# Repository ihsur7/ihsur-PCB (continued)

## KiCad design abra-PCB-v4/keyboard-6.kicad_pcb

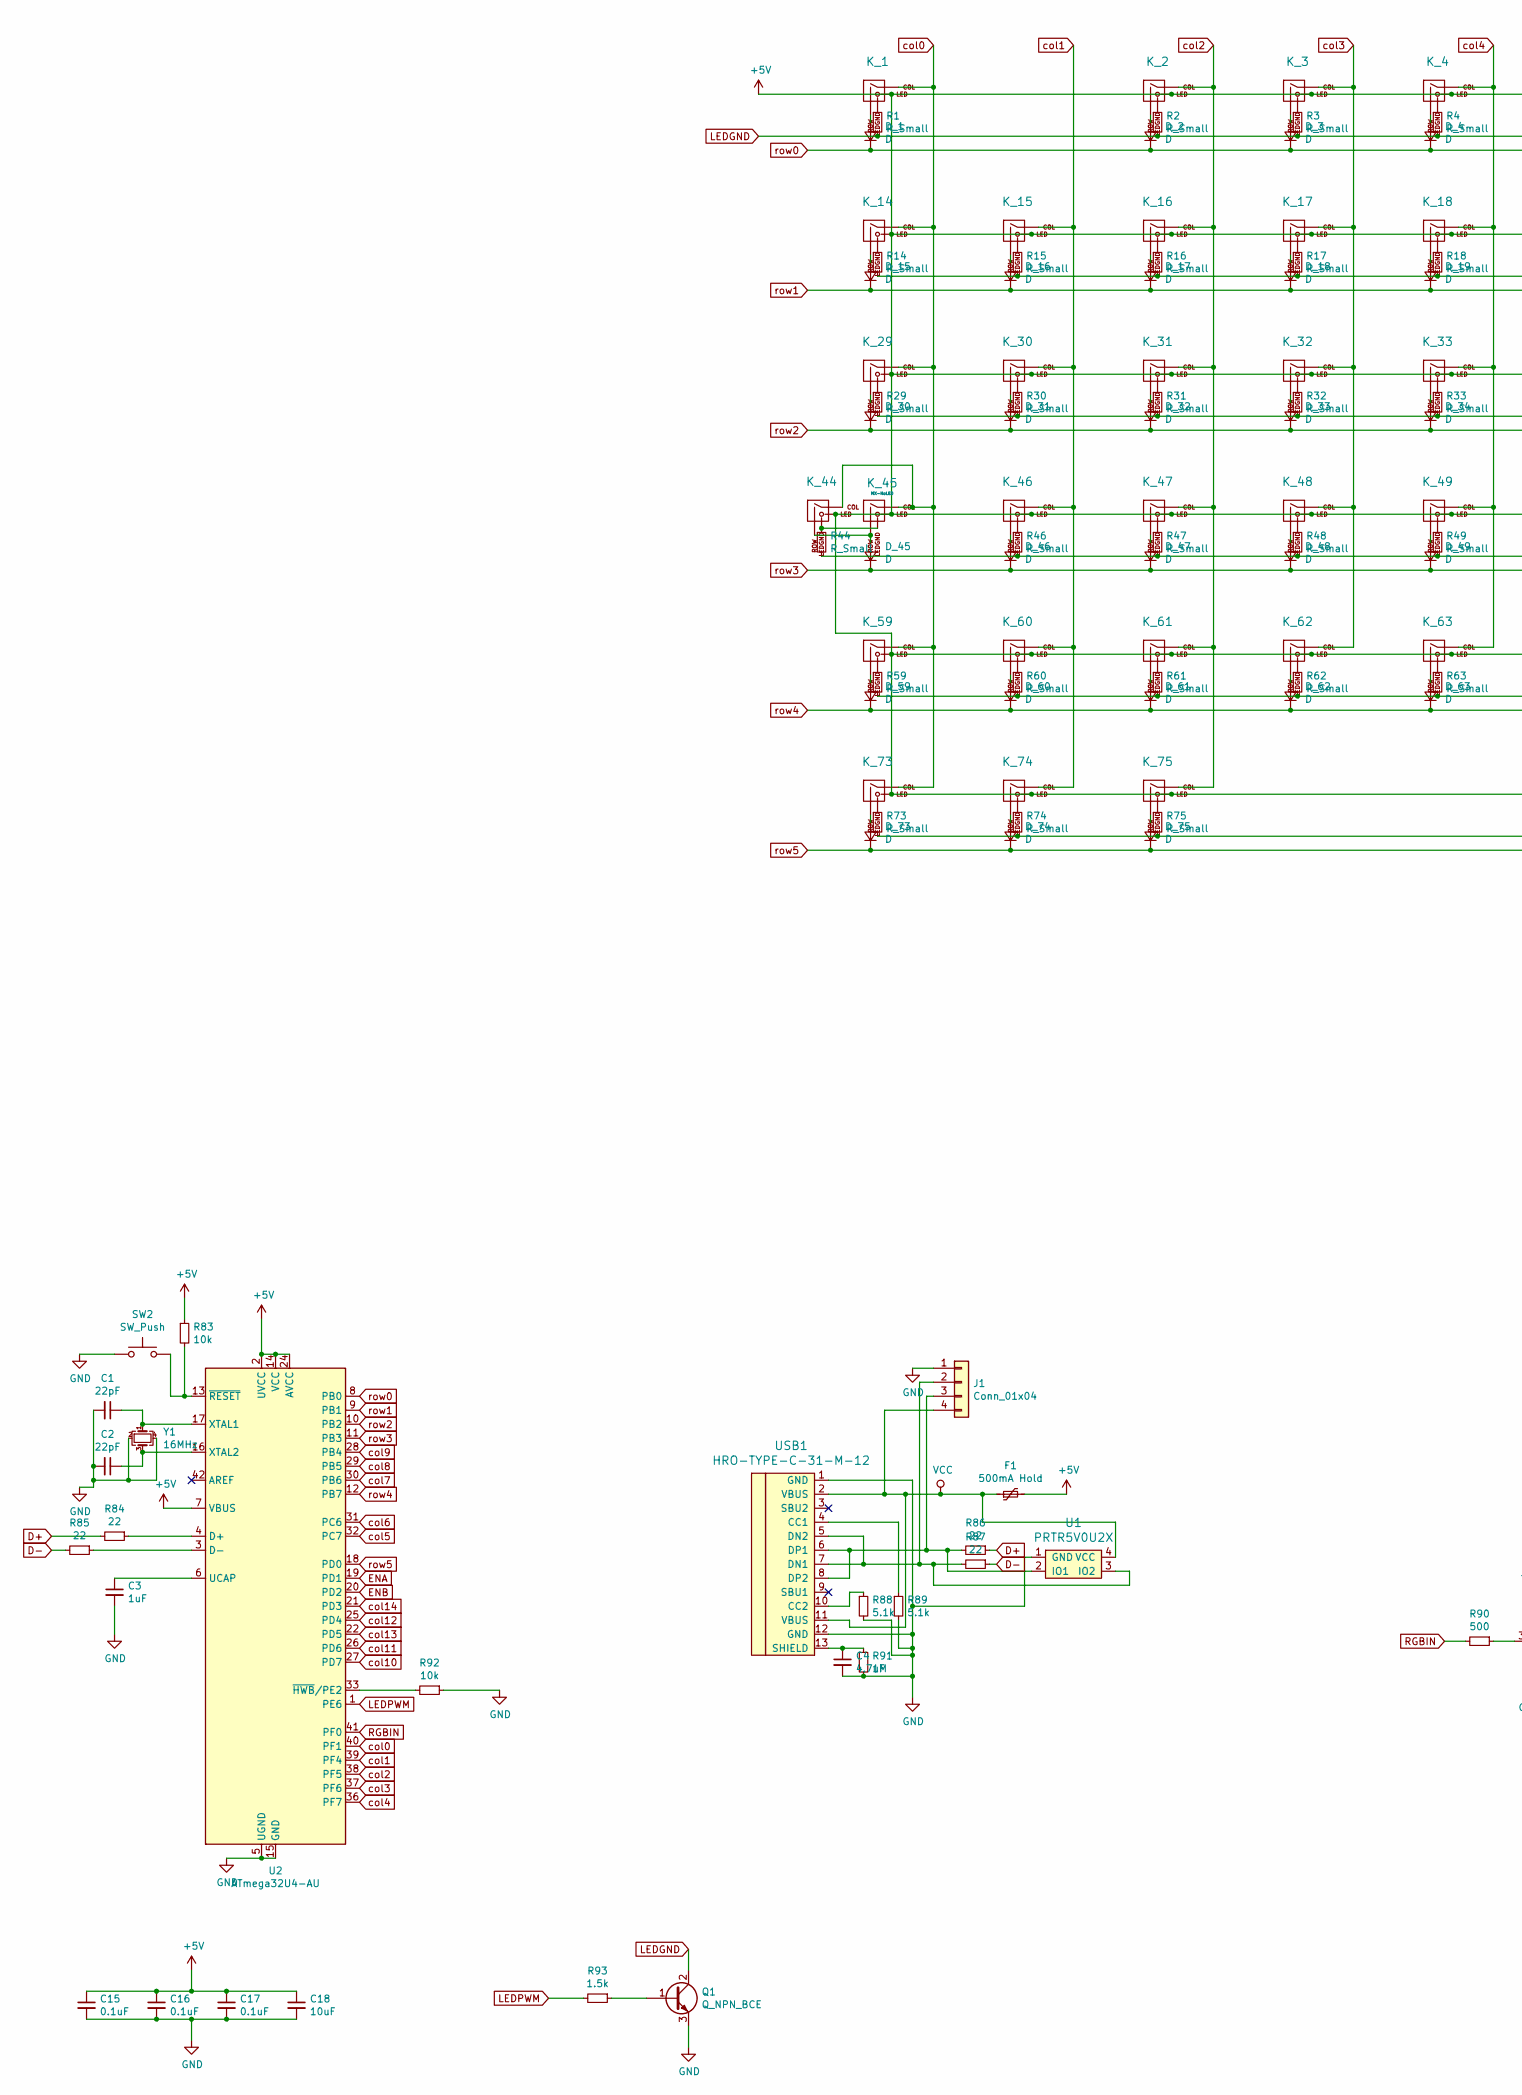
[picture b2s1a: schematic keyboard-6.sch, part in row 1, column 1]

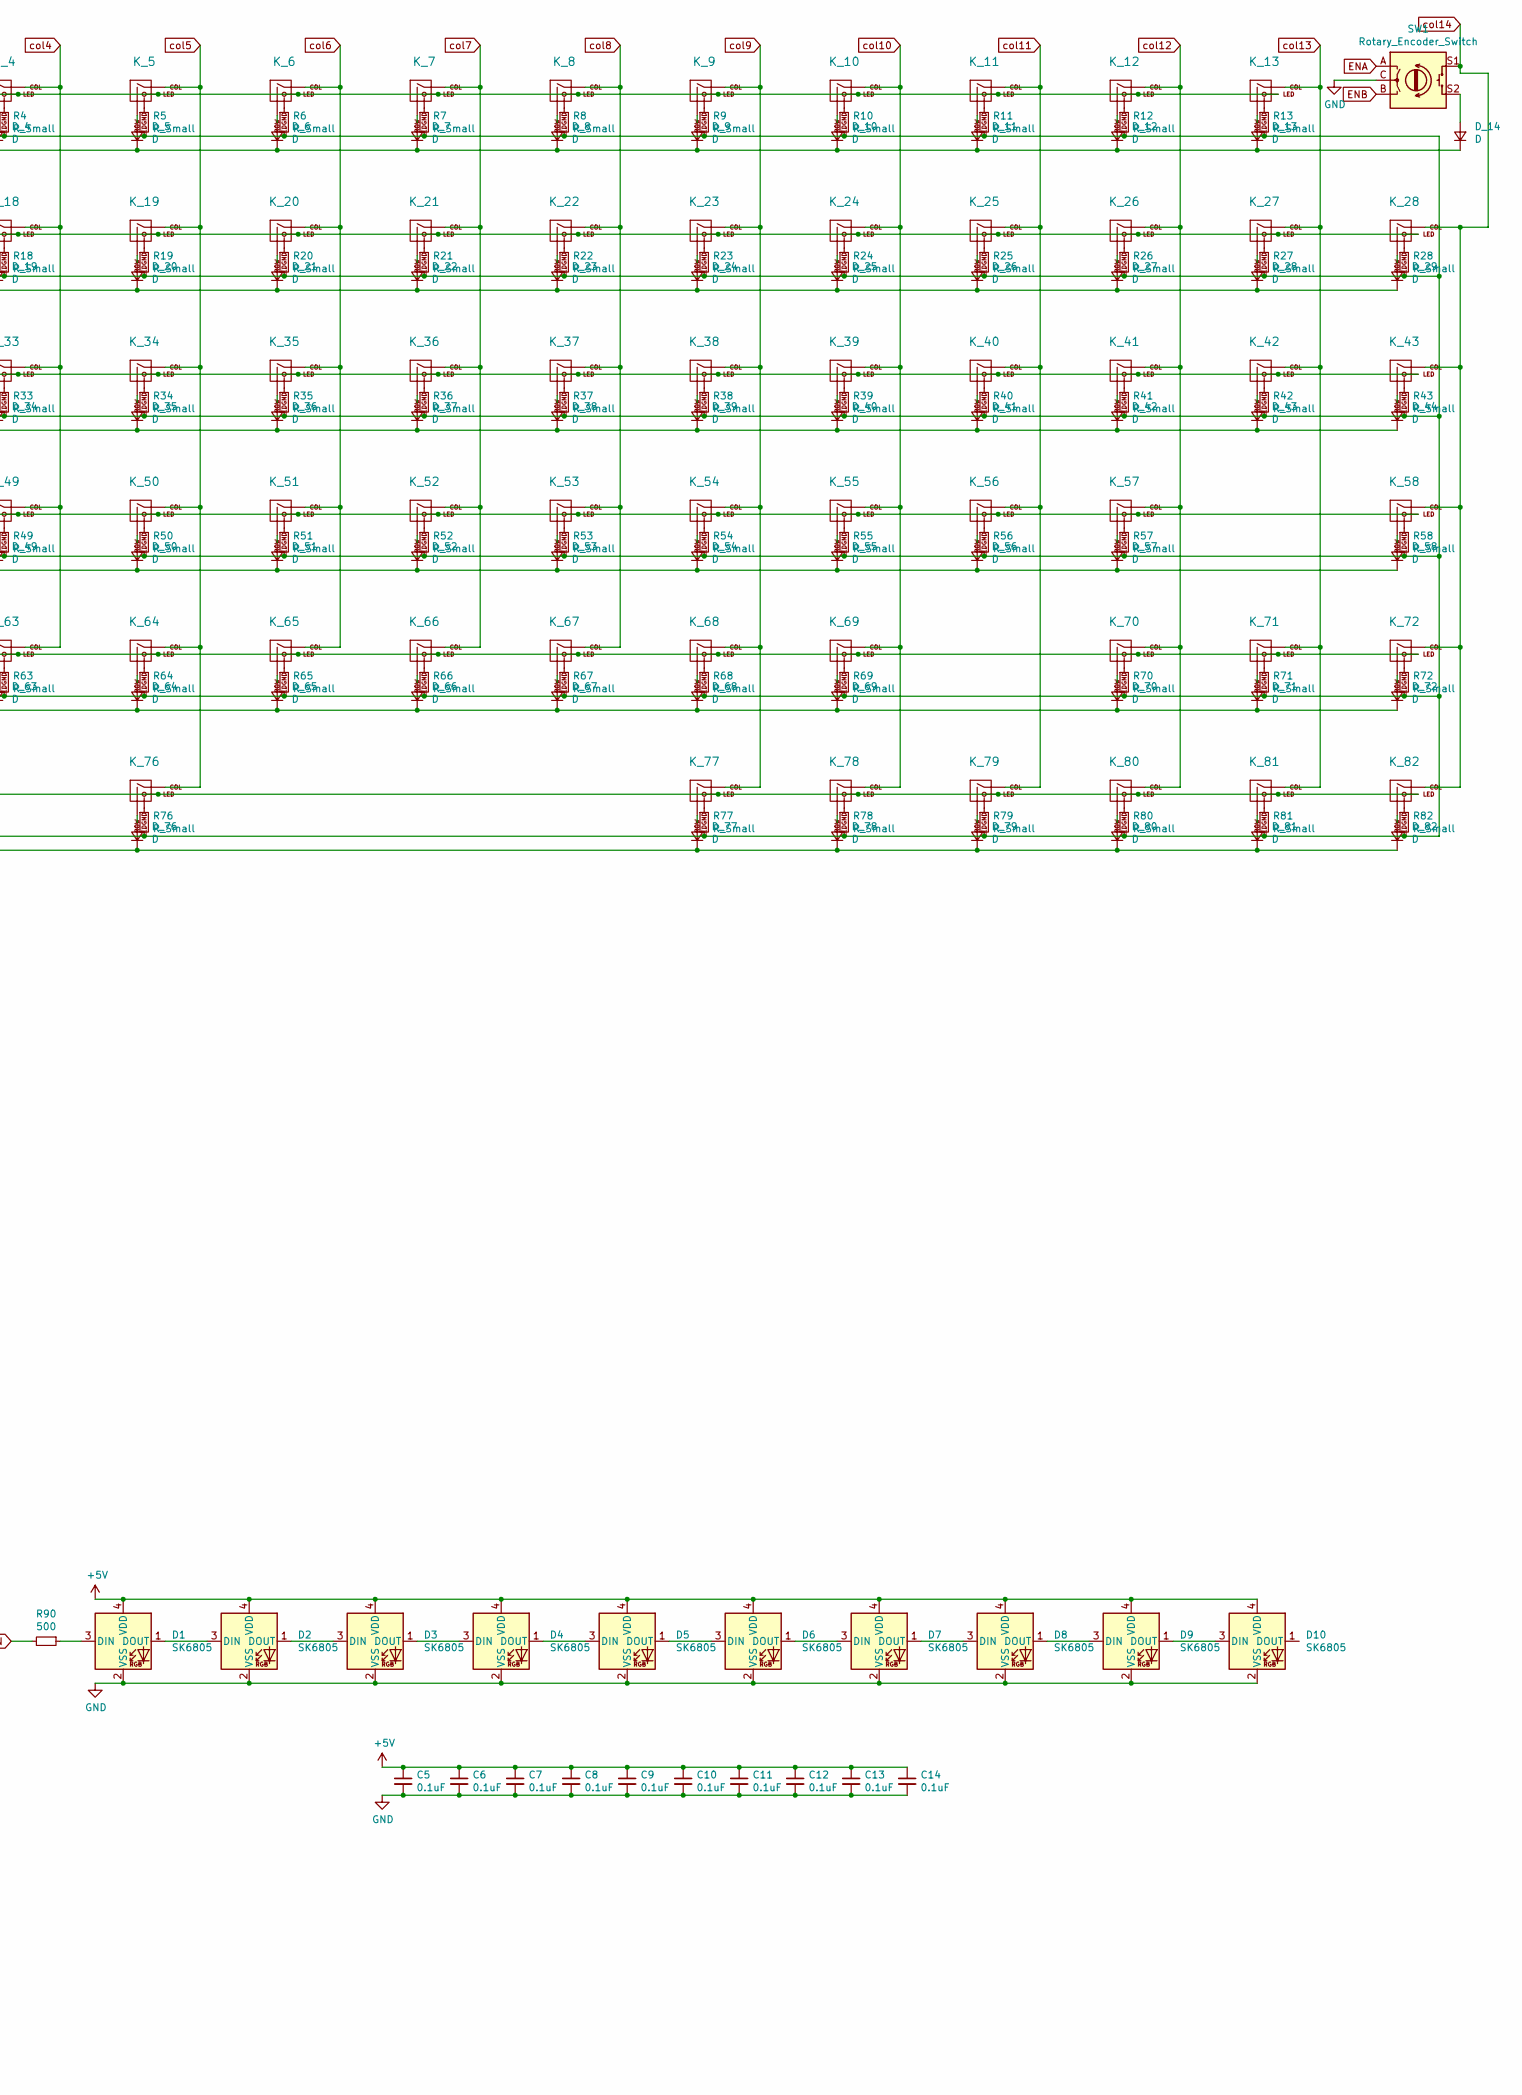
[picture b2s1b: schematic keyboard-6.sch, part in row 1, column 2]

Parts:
C1, C2: 22pF; C_0805_2012Metric
C3: 1uF; C_0805_2012Metric
C4: 4.7uF; C_0805_2012Metric
C5, C6, C7, C8, C9, C10, C11, C12, C13, C14, C15, C16, C17: 0.1uF; C_0805_2012Metric
C18: 10uF; C_0805_2012Metric
D1, D2, D3, D4, D5, D6, D7, D8, D9, D10: SK6805; LED_SK6812_EC15_1.5x1.5mm
D_1, D_2, D_3, D_4, D_5, D_6, D_7, D_8, D_9, D_10, D_11, D_12, D_13, D_14, D_15, D_16, D_17, D_18, D_19, D_20, D_21, D_22, D_23, D_24, D_25, D_26, D_27, D_28, D_29, D_30, D_31, D_32, D_33, D_34, D_35, D_36, D_37, D_38, D_39, D_40, D_41, D_42, D_43, D_44, D_45, D_46, D_47, D_48, D_49, D_50, D_51, D_52, D_53, D_54, D_55, D_56, D_57, D_58, D_59, D_60, D_61, D_62, D_63, D_64, D_65, D_66, D_67, D_68, D_69, D_70, D_71, D_72, D_73, D_74, D_75, D_76, D_77, D_78, D_79, D_80, D_81, D_82: D; D_SOD-123
F1: 500mA Hold; Fuse_1812_4532
J1: Conn_01x04; PinHeader_1x04_P2.54mm_Vertical_SMD_Pin1Left
K_1, K_2, K_3, K_4, K_5, K_6, K_7, K_8, K_9, K_10, K_11, K_12, K_13, K_14, K_15, K_16, K_17, K_18, K_19, K_20, K_21, K_22, K_23, K_24, K_25, K_26, K_28, K_30, K_31, K_32, K_33, K_34, K_35, K_36, K_37, K_38, K_39, K_40, K_41, K_43, K_46, K_47, K_48, K_49, K_50, K_51, K_52, K_53, K_54, K_55, K_56, K_58, K_60, K_61, K_62, K_63, K_64, K_65, K_66, K_67, K_68, K_69, K_71, K_72, K_77, K_78, K_79, K_80, K_81, K_82: KEYSW; MXOnly-1U
K_27: KEYSW; MXOnly-2U
K_29, K_42: KEYSW; MXOnly-1.5U
K_44, K_70: KEYSW; MXOnly-1.75U
K_45: MX-NoLED; MXOnly-1.75U
K_57, K_59: KEYSW; MXOnly-2.25U
K_73, K_74, K_75: KEYSW; MXOnly-1.25U
K_76: KEYSW; MXOnly-6.25U
Q1: Q_NPN_BCE; SOT-223-3_TabPin2
R1, R2, R3, R4, R5, R6, R7, R8, R9, R10, R11, R12, R13, R14, R15, R16, R17, R18, R19, R20, R21, R22, R23, R24, R25, R26, R27, R28, R29, R30, R31, R32, R33, R34, R35, R36, R37, R38, R39, R40, R41, R42, R43, R44, R46, R47, R48, R49, R50, R51, R52, R53, R54, R55, R56, R57, R58, R59, R60, R61, R62, R63, R64, R65, R66, R67, R68, R69, R70, R71, R72, R73, R74, R75, R76, R77, R78, R79, R80, R81, R82: R_Small; R_SMD_1206
R83, R92: 10k; R_SMD_1206
R84, R85, R86, R87: 22; R_SMD_1206
R88, R89: 5.1k; R_SMD_1206
R90: 500; R_SMD_1206
R91: 1M; R_SMD_1206
R93: 1.5k; R_SMD_1206
SW1: Rotary_Encoder_Switch; RotaryEncoder_Alps_EC11E-Switch_Vertical_H20mm
SW2: SW_Push; SW_SPST_3x3
U1: PRTR5V0U2X; SOT143B
U2: ATmega32U4-AU; TQFP-44_10x10mm_P0.8mm
USB1: HRO-TYPE-C-31-M-12; HRO-TYPE-C-31-M-12-HandSoldering
Y1: 16MHz; Crystal_SMD_3225-4pin_3.2x2.5mm

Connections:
+5V: C5.1, C6.1, C7.1, C8.1, C9.1, C10.1, C11.1, C12.1, C13.1, C14.1, C15.1, C16.1, C17.1, C18.1, D1.4 (VDD), D2.4 (VDD), D3.4 (VDD), D4.4 (VDD), D5.4 (VDD), D6.4 (VDD), D7.4 (VDD), D8.4 (VDD), D9.4 (VDD), D10.4 (VDD), F1.2, K_1.3 (LED), K_2.3 (LED), K_3.3 (LED), K_4.3 (LED), K_5.3 (LED), K_6.3 (LED), K_7.3 (LED), K_8.3 (LED), K_9.3 (LED), K_10.3 (LED), K_11.3 (LED), K_12.3 (LED), K_13.3 (LED), K_14.3 (LED), K_15.3 (LED), K_16.3 (LED), K_17.3 (LED), K_18.3 (LED), K_19.3 (LED), K_20.3 (LED), K_21.3 (LED), K_22.3 (LED), K_23.3 (LED), K_24.3 (LED), K_25.3 (LED), K_26.3 (LED), K_27.3 (LED), K_28.3 (LED), K_29.3 (LED), K_30.3 (LED), K_31.3 (LED), K_32.3 (LED), K_33.3 (LED), K_34.3 (LED), K_35.3 (LED), K_36.3 (LED), K_37.3 (LED), K_38.3 (LED), K_39.3 (LED), K_40.3 (LED), K_41.3 (LED), K_42.3 (LED), K_43.3 (LED), K_44.3 (LED), K_45.3 (LED), K_46.3 (LED), K_47.3 (LED), K_48.3 (LED), K_49.3 (LED), K_50.3 (LED), K_51.3 (LED), K_52.3 (LED), K_53.3 (LED), K_54.3 (LED), K_55.3 (LED), K_56.3 (LED), K_57.3 (LED), K_58.3 (LED), K_59.3 (LED), K_60.3 (LED), K_61.3 (LED), K_62.3 (LED), K_63.3 (LED), K_64.3 (LED), K_65.3 (LED), K_66.3 (LED), K_67.3 (LED), K_68.3 (LED), K_69.3 (LED), K_70.3 (LED), K_71.3 (LED), K_72.3 (LED), K_73.3 (LED), K_74.3 (LED), K_75.3 (LED), K_76.3 (LED), K_77.3 (LED), K_78.3 (LED), K_79.3 (LED), K_80.3 (LED), K_81.3 (LED), K_82.3 (LED), R83.1, U2.2 (UVCC), U2.7 (VBUS), U2.14 (VCC), U2.24 (AVCC), U2.34 (VCC), U2.44 (AVCC)
D+: R84.2, R86.1
D-: R85.2, R87.1
ENA: SW1.A, U2.19 (PD1)
ENB: SW1.B, U2.20 (PD2)
GND: C1.2, C2.2, C3.2, C4.2, C5.2, C6.2, C7.2, C8.2, C9.2, C10.2, C11.2, C12.2, C13.2, C14.2, C15.2, C16.2, C17.2, C18.2, D1.2 (VSS), D2.2 (VSS), D3.2 (VSS), D4.2 (VSS), D5.2 (VSS), D6.2 (VSS), D7.2 (VSS), D8.2 (VSS), D9.2 (VSS), D10.2 (VSS), J1.1, Q1.3 (E), R88.2, R89.2, R91.2, R92.1, SW1.C, SW2.1, U1.1 (GND), U2.5 (UGND), U2.15 (GND), U2.23 (GND), U2.35 (GND), U2.43 (GND), USB1.1 (GND), USB1.12 (GND), Y1.2, Y1.4
LEDGND: Q1.2 (C), R1.2, R2.2, R3.2, R4.2, R5.2, R6.2, R7.2, R8.2, R9.2, R10.2, R11.2, R12.2, R13.2, R14.2, R15.2, R16.2, R17.2, R18.2, R19.2, R20.2, R21.2, R22.2, R23.2, R24.2, R25.2, R26.2, R27.2, R28.2, R29.2, R30.2, R31.2, R32.2, R33.2, R34.2, R35.2, R36.2, R37.2, R38.2, R39.2, R40.2, R41.2, R42.2, R43.2, R44.2, R46.2, R47.2, R48.2, R49.2, R50.2, R51.2, R52.2, R53.2, R54.2, R55.2, R56.2, R57.2, R58.2, R59.2, R60.2, R61.2, R62.2, R63.2, R64.2, R65.2, R66.2, R67.2, R68.2, R69.2, R70.2, R71.2, R72.2, R73.2, R74.2, R75.2, R76.2, R77.2, R78.2, R79.2, R80.2, R81.2, R82.2
LEDPWM: R93.2, U2.1 (PE6)
unnamed: C1.1, U2.17 (XTAL1), Y1.1
unnamed: C2.1, U2.16 (XTAL2), Y1.3
unnamed: C3.1, U2.6 (UCAP)
unnamed: C4.1, R91.1, USB1.13 (SHIELD)
unnamed: D1.1 (DOUT), D2.3 (DIN)
unnamed: D1.3 (DIN), R90.1
unnamed: D2.1 (DOUT), D3.3 (DIN)
unnamed: D3.1 (DOUT), D4.3 (DIN)
unnamed: D4.1 (DOUT), D5.3 (DIN)
unnamed: D5.1 (DOUT), D6.3 (DIN)
unnamed: D6.1 (DOUT), D7.3 (DIN)
unnamed: D7.1 (DOUT), D8.3 (DIN)
unnamed: D8.1 (DOUT), D9.3 (DIN)
unnamed: D9.1 (DOUT), D10.3 (DIN)
unnamed: D_1.2 (A), K_1.2 (ROW)
unnamed: D_2.2 (A), K_2.2 (ROW)
unnamed: D_3.2 (A), K_3.2 (ROW)
unnamed: D_4.2 (A), K_4.2 (ROW)
unnamed: D_5.2 (A), K_5.2 (ROW)
unnamed: D_6.2 (A), K_6.2 (ROW)
unnamed: D_7.2 (A), K_7.2 (ROW)
unnamed: D_8.2 (A), K_8.2 (ROW)
unnamed: D_9.2 (A), K_9.2 (ROW)
unnamed: D_10.2 (A), K_10.2 (ROW)
unnamed: D_11.2 (A), K_11.2 (ROW)
unnamed: D_12.2 (A), K_12.2 (ROW)
unnamed: D_13.2 (A), K_13.2 (ROW)
unnamed: D_14.2 (A), SW1.S2
unnamed: D_15.2 (A), K_14.2 (ROW)
unnamed: D_16.2 (A), K_15.2 (ROW)
unnamed: D_17.2 (A), K_16.2 (ROW)
unnamed: D_18.2 (A), K_17.2 (ROW)
unnamed: D_19.2 (A), K_18.2 (ROW)
unnamed: D_20.2 (A), K_19.2 (ROW)
unnamed: D_21.2 (A), K_20.2 (ROW)
unnamed: D_22.2 (A), K_21.2 (ROW)
unnamed: D_23.2 (A), K_22.2 (ROW)
unnamed: D_24.2 (A), K_23.2 (ROW)
unnamed: D_25.2 (A), K_24.2 (ROW)
unnamed: D_26.2 (A), K_25.2 (ROW)
unnamed: D_27.2 (A), K_26.2 (ROW)
unnamed: D_28.2 (A), K_27.2 (ROW)
unnamed: D_29.2 (A), K_28.2 (ROW)
unnamed: D_30.2 (A), K_29.2 (ROW)
unnamed: D_31.2 (A), K_30.2 (ROW)
unnamed: D_32.2 (A), K_31.2 (ROW)
unnamed: D_33.2 (A), K_32.2 (ROW)
unnamed: D_34.2 (A), K_33.2 (ROW)
unnamed: D_35.2 (A), K_34.2 (ROW)
unnamed: D_36.2 (A), K_35.2 (ROW)
unnamed: D_37.2 (A), K_36.2 (ROW)
unnamed: D_38.2 (A), K_37.2 (ROW)
unnamed: D_39.2 (A), K_38.2 (ROW)
unnamed: D_40.2 (A), K_39.2 (ROW)
unnamed: D_41.2 (A), K_40.2 (ROW)
unnamed: D_42.2 (A), K_41.2 (ROW)
unnamed: D_43.2 (A), K_42.2 (ROW)
unnamed: D_44.2 (A), K_43.2 (ROW)
unnamed: D_45.2 (A), K_44.2 (ROW), K_45.2 (ROW)
unnamed: D_46.2 (A), K_46.2 (ROW)
unnamed: D_47.2 (A), K_47.2 (ROW)
unnamed: D_48.2 (A), K_48.2 (ROW)
unnamed: D_49.2 (A), K_49.2 (ROW)
unnamed: D_50.2 (A), K_50.2 (ROW)
unnamed: D_51.2 (A), K_51.2 (ROW)
unnamed: D_52.2 (A), K_52.2 (ROW)
unnamed: D_53.2 (A), K_53.2 (ROW)
unnamed: D_54.2 (A), K_54.2 (ROW)
unnamed: D_55.2 (A), K_55.2 (ROW)
unnamed: D_56.2 (A), K_56.2 (ROW)
unnamed: D_57.2 (A), K_57.2 (ROW)
unnamed: D_58.2 (A), K_58.2 (ROW)
unnamed: D_59.2 (A), K_59.2 (ROW)
unnamed: D_60.2 (A), K_60.2 (ROW)
unnamed: D_61.2 (A), K_61.2 (ROW)
unnamed: D_62.2 (A), K_62.2 (ROW)
unnamed: D_63.2 (A), K_63.2 (ROW)
unnamed: D_64.2 (A), K_64.2 (ROW)
unnamed: D_65.2 (A), K_65.2 (ROW)
unnamed: D_66.2 (A), K_66.2 (ROW)
unnamed: D_67.2 (A), K_67.2 (ROW)
unnamed: D_68.2 (A), K_68.2 (ROW)
unnamed: D_69.2 (A), K_69.2 (ROW)
unnamed: D_70.2 (A), K_70.2 (ROW)
unnamed: D_71.2 (A), K_71.2 (ROW)
unnamed: D_72.2 (A), K_72.2 (ROW)
unnamed: D_73.2 (A), K_73.2 (ROW)
unnamed: D_74.2 (A), K_74.2 (ROW)
unnamed: D_75.2 (A), K_75.2 (ROW)
unnamed: D_76.2 (A), K_76.2 (ROW)
unnamed: D_77.2 (A), K_77.2 (ROW)
unnamed: D_78.2 (A), K_78.2 (ROW)
unnamed: D_79.2 (A), K_79.2 (ROW)
unnamed: D_80.2 (A), K_80.2 (ROW)
unnamed: D_81.2 (A), K_81.2 (ROW)
unnamed: D_82.2 (A), K_82.2 (ROW)
unnamed: J1.2, R87.2, U1.3 (IO2), USB1.5 (DN2), USB1.7 (DN1)
unnamed: J1.3, R86.2, U1.2 (IO1), USB1.6 (DP1), USB1.8 (DP2)
unnamed: K_1.4 (LEDGND), R1.1
unnamed: K_2.4 (LEDGND), R2.1
unnamed: K_3.4 (LEDGND), R3.1
unnamed: K_4.4 (LEDGND), R4.1
unnamed: K_5.4 (LEDGND), R5.1
unnamed: K_6.4 (LEDGND), R6.1
unnamed: K_7.4 (LEDGND), R7.1
unnamed: K_8.4 (LEDGND), R8.1
unnamed: K_9.4 (LEDGND), R9.1
unnamed: K_10.4 (LEDGND), R10.1
unnamed: K_11.4 (LEDGND), R11.1
unnamed: K_12.4 (LEDGND), R12.1
unnamed: K_13.4 (LEDGND), R13.1
unnamed: K_14.4 (LEDGND), R14.1
unnamed: K_15.4 (LEDGND), R15.1
unnamed: K_16.4 (LEDGND), R16.1
unnamed: K_17.4 (LEDGND), R17.1
unnamed: K_18.4 (LEDGND), R18.1
unnamed: K_19.4 (LEDGND), R19.1
unnamed: K_20.4 (LEDGND), R20.1
unnamed: K_21.4 (LEDGND), R21.1
unnamed: K_22.4 (LEDGND), R22.1
unnamed: K_23.4 (LEDGND), R23.1
unnamed: K_24.4 (LEDGND), R24.1
unnamed: K_25.4 (LEDGND), R25.1
unnamed: K_26.4 (LEDGND), R26.1
unnamed: K_27.4 (LEDGND), R27.1
unnamed: K_28.4 (LEDGND), R28.1
unnamed: K_29.4 (LEDGND), R29.1
unnamed: K_30.4 (LEDGND), R30.1
unnamed: K_31.4 (LEDGND), R31.1
unnamed: K_32.4 (LEDGND), R32.1
unnamed: K_33.4 (LEDGND), R33.1
unnamed: K_34.4 (LEDGND), R34.1
unnamed: K_35.4 (LEDGND), R35.1
unnamed: K_36.4 (LEDGND), R36.1
unnamed: K_37.4 (LEDGND), R37.1
unnamed: K_38.4 (LEDGND), R38.1
unnamed: K_39.4 (LEDGND), R39.1
unnamed: K_40.4 (LEDGND), R40.1
unnamed: K_41.4 (LEDGND), R41.1
unnamed: K_42.4 (LEDGND), R42.1
unnamed: K_43.4 (LEDGND), R43.1
unnamed: K_44.4 (LEDGND), K_45.4 (LEDGND), R44.1
unnamed: K_46.4 (LEDGND), R46.1
unnamed: K_47.4 (LEDGND), R47.1
unnamed: K_48.4 (LEDGND), R48.1
unnamed: K_49.4 (LEDGND), R49.1
unnamed: K_50.4 (LEDGND), R50.1
unnamed: K_51.4 (LEDGND), R51.1
unnamed: K_52.4 (LEDGND), R52.1
unnamed: K_53.4 (LEDGND), R53.1
unnamed: K_54.4 (LEDGND), R54.1
unnamed: K_55.4 (LEDGND), R55.1
unnamed: K_56.4 (LEDGND), R56.1
unnamed: K_57.4 (LEDGND), R57.1
unnamed: K_58.4 (LEDGND), R58.1
unnamed: K_59.4 (LEDGND), R59.1
unnamed: K_60.4 (LEDGND), R60.1
unnamed: K_61.4 (LEDGND), R61.1
unnamed: K_62.4 (LEDGND), R62.1
unnamed: K_63.4 (LEDGND), R63.1
unnamed: K_64.4 (LEDGND), R64.1
unnamed: K_65.4 (LEDGND), R65.1
unnamed: K_66.4 (LEDGND), R66.1
unnamed: K_67.4 (LEDGND), R67.1
unnamed: K_68.4 (LEDGND), R68.1
unnamed: K_69.4 (LEDGND), R69.1
unnamed: K_70.4 (LEDGND), R70.1
unnamed: K_71.4 (LEDGND), R71.1
unnamed: K_72.4 (LEDGND), R72.1
unnamed: K_73.4 (LEDGND), R73.1
unnamed: K_74.4 (LEDGND), R74.1
unnamed: K_75.4 (LEDGND), R75.1
unnamed: K_76.4 (LEDGND), R76.1
unnamed: K_77.4 (LEDGND), R77.1
unnamed: K_78.4 (LEDGND), R78.1
unnamed: K_79.4 (LEDGND), R79.1
unnamed: K_80.4 (LEDGND), R80.1
unnamed: K_81.4 (LEDGND), R81.1
unnamed: K_82.4 (LEDGND), R82.1
unnamed: Q1.1 (B), R93.1
unnamed: R83.2, SW2.2, U2.13 (~RESET)
unnamed: R84.1, U2.4 (D+)
unnamed: R85.1, U2.3 (D-)
unnamed: R88.1, USB1.10 (CC2)
unnamed: R89.1, USB1.4 (CC1)
unnamed: R92.2, U2.33 (~HWB~/PE2)
RGBIN: R90.2, U2.41 (PF0)
VCC: F1.1, J1.4, U1.4 (VCC), USB1.2 (VBUS), USB1.11 (VBUS)
col0: K_1.1 (COL), K_14.1 (COL), K_29.1 (COL), K_44.1 (COL), K_45.1 (COL), K_59.1 (COL), K_73.1 (COL), U2.40 (PF1)
col1: K_15.1 (COL), K_30.1 (COL), K_46.1 (COL), K_60.1 (COL), K_74.1 (COL), U2.39 (PF4)
col2: K_2.1 (COL), K_16.1 (COL), K_31.1 (COL), K_47.1 (COL), K_61.1 (COL), K_75.1 (COL), U2.38 (PF5)
col3: K_3.1 (COL), K_17.1 (COL), K_32.1 (COL), K_48.1 (COL), K_62.1 (COL), U2.37 (PF6)
col4: K_4.1 (COL), K_18.1 (COL), K_33.1 (COL), K_49.1 (COL), K_63.1 (COL), U2.36 (PF7)
col5: K_5.1 (COL), K_19.1 (COL), K_34.1 (COL), K_50.1 (COL), K_64.1 (COL), K_76.1 (COL), U2.32 (PC7)
col6: K_6.1 (COL), K_20.1 (COL), K_35.1 (COL), K_51.1 (COL), K_65.1 (COL), U2.31 (PC6)
col7: K_7.1 (COL), K_21.1 (COL), K_36.1 (COL), K_52.1 (COL), K_66.1 (COL), U2.30 (PB6)
col8: K_8.1 (COL), K_22.1 (COL), K_37.1 (COL), K_53.1 (COL), K_67.1 (COL), U2.29 (PB5)
col9: K_9.1 (COL), K_23.1 (COL), K_38.1 (COL), K_54.1 (COL), K_68.1 (COL), K_77.1 (COL), U2.28 (PB4)
col10: K_10.1 (COL), K_24.1 (COL), K_39.1 (COL), K_55.1 (COL), K_69.1 (COL), K_78.1 (COL), U2.27 (PD7)
col11: K_11.1 (COL), K_25.1 (COL), K_40.1 (COL), K_56.1 (COL), K_79.1 (COL), U2.26 (PD6)
col12: K_12.1 (COL), K_26.1 (COL), K_41.1 (COL), K_57.1 (COL), K_70.1 (COL), K_80.1 (COL), U2.25 (PD4)
col13: K_13.1 (COL), K_27.1 (COL), K_42.1 (COL), K_71.1 (COL), K_81.1 (COL), U2.22 (PD5)
col14: K_28.1 (COL), K_43.1 (COL), K_58.1 (COL), K_72.1 (COL), K_82.1 (COL), SW1.S1, U2.21 (PD3)
row0: D_1.1 (K), D_2.1 (K), D_3.1 (K), D_4.1 (K), D_5.1 (K), D_6.1 (K), D_7.1 (K), D_8.1 (K), D_9.1 (K), D_10.1 (K), D_11.1 (K), D_12.1 (K), D_13.1 (K), D_14.1 (K), U2.8 (PB0)
row1: D_15.1 (K), D_16.1 (K), D_17.1 (K), D_18.1 (K), D_19.1 (K), D_20.1 (K), D_21.1 (K), D_22.1 (K), D_23.1 (K), D_24.1 (K), D_25.1 (K), D_26.1 (K), D_27.1 (K), D_28.1 (K), D_29.1 (K), U2.9 (PB1)
row2: D_30.1 (K), D_31.1 (K), D_32.1 (K), D_33.1 (K), D_34.1 (K), D_35.1 (K), D_36.1 (K), D_37.1 (K), D_38.1 (K), D_39.1 (K), D_40.1 (K), D_41.1 (K), D_42.1 (K), D_43.1 (K), D_44.1 (K), U2.10 (PB2)
row3: D_45.1 (K), D_46.1 (K), D_47.1 (K), D_48.1 (K), D_49.1 (K), D_50.1 (K), D_51.1 (K), D_52.1 (K), D_53.1 (K), D_54.1 (K), D_55.1 (K), D_56.1 (K), D_57.1 (K), D_58.1 (K), U2.11 (PB3)
row4: D_59.1 (K), D_60.1 (K), D_61.1 (K), D_62.1 (K), D_63.1 (K), D_64.1 (K), D_65.1 (K), D_66.1 (K), D_67.1 (K), D_68.1 (K), D_69.1 (K), D_70.1 (K), D_71.1 (K), D_72.1 (K), U2.12 (PB7)
row5: D_73.1 (K), D_74.1 (K), D_75.1 (K), D_76.1 (K), D_77.1 (K), D_78.1 (K), D_79.1 (K), D_80.1 (K), D_81.1 (K), D_82.1 (K), U2.18 (PD0)

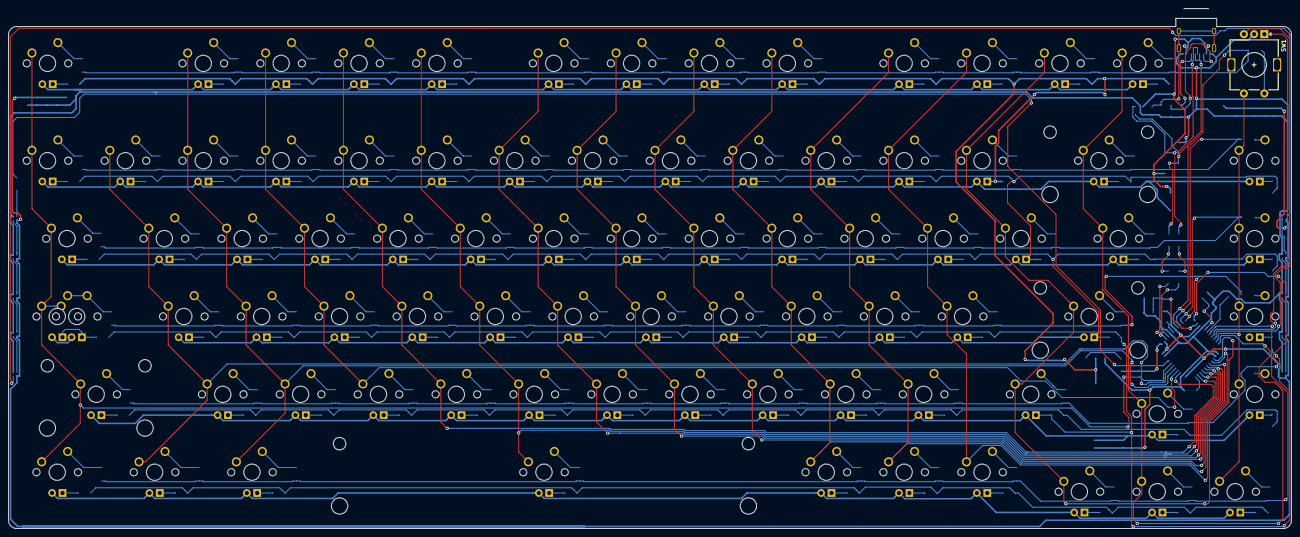
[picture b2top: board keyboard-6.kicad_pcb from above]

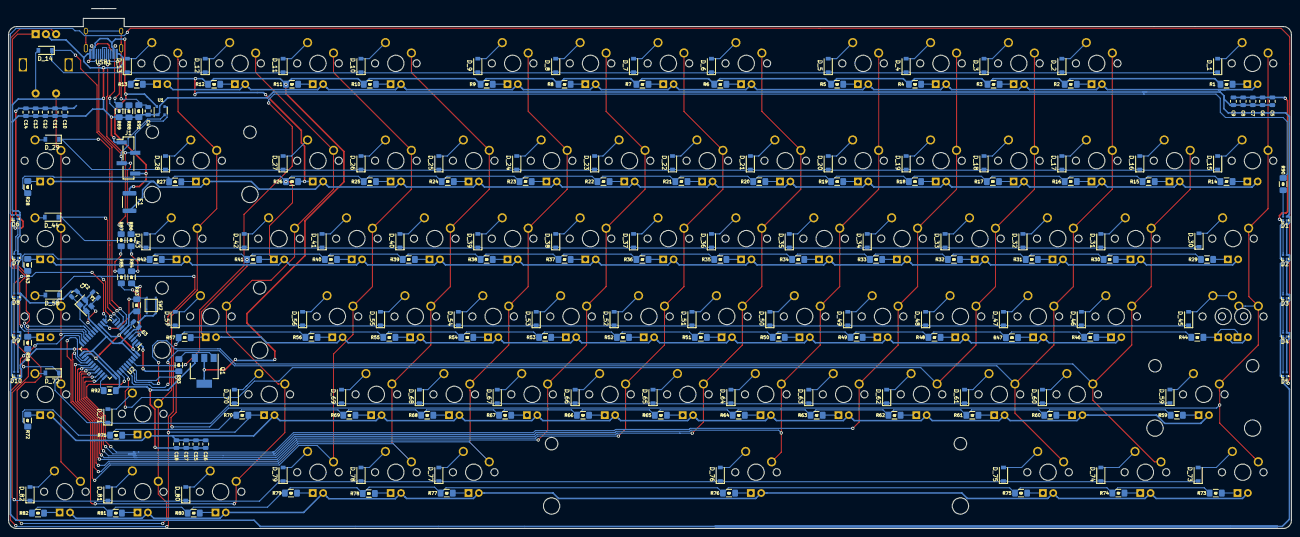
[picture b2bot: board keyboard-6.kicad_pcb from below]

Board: 2 copper layers, 313.8 x 127.2 mm, 293 parts (210 on the bottom side), 217 nets.

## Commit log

2020-07-20 add submodules
2020-07-20 add footprint libraries
2020-07-20 added atmega mcu
2020-07-21 added autogenerated schematic
2020-07-22 added mx keys
2020-07-22 v4 update - footprint fix
2020-07-23 added usb + mcu
2020-07-23 updated schematic
2020-07-27 added underglow and backlighting
2020-07-28 layout changes
2020-07-28 layout updates
2020-09-08 light fix + library update
2020-09-09 routing updates
2020-09-10 fully connected v3, updated location v4
2020-09-10 version 4
2020-09-11 v4 routing complete
2020-09-11 routing update
2020-09-16 pcb updates
2020-09-16 fixed capacitors, need to increase power traces width
2020-09-20 gerber export
2020-10-20 backspace fix led spacing update
